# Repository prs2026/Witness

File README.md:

# Witness
Witness flight computer

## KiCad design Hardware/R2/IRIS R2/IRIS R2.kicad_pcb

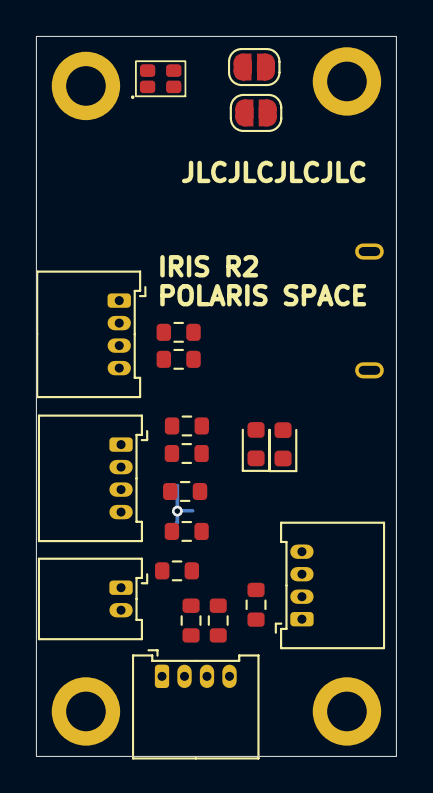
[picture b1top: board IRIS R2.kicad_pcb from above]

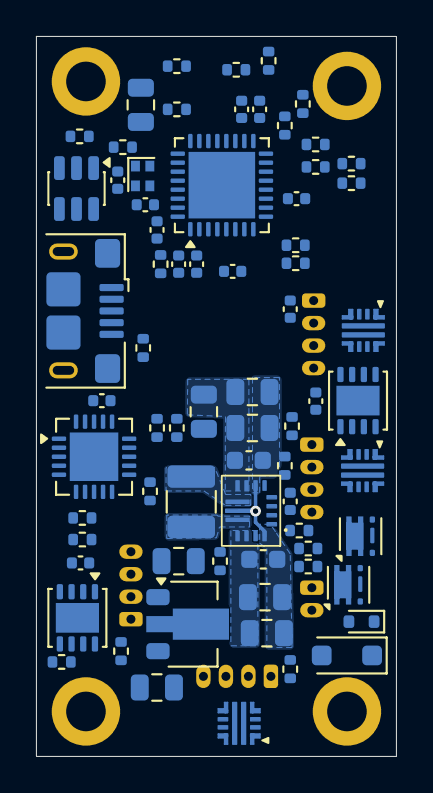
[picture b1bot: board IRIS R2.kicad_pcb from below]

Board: 4 copper layers, 20.0 x 40.0 mm, 95 parts (71 on the bottom side), 65 nets.

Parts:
C3, C4, C5, C7, C8, C9, C13, C21, C26, C27, C28, C29, C30: 100n; C_0402_1005Metric
C6: 1u; C_0402_1005Metric
C10, C11, C12, C18, C19: 10u; C_0805_2012Metric
C20, C22: 10u; C_0603_1608Metric
C23, C24, C25: 22u; C_0805_2012Metric
D1: LED_RGBA; 0603x2 RGB
D2, D3: LED; LED_0603_1608Metric
D4: PMEG2020EH,115; D_SOD-123F
D5: BZX584C10; D_SOD-523
H4, H5, H6, H7: MountingHole_Pad; MountingHole_2.2mm_M2_DIN965_Pad
J1, J4: Conn_01x02; SolderJumper-2_P1.3mm_Open_RoundedPad1.0x1.5mm
J2: Conn_01x02; Molex_Micro_Lock_2200980271_01x02_Horizontal
J3: USB_B_Micro; USB_Micro-B_Amphenol_10118193-0002LF_Horizontal
J5, J6, J7, J8: Conn_01x04; Molex_MicroLock-2200980471-01x04-Horizontal
L3: 1u; L_1210_3225Metric
Q1, Q2: SQA403EJ; Vishay_PowerPAK_SC70-6L_Single
R1, R2, R3, R4, R5, R11, R13: 0; R_0603_1608Metric
R6, R10, R12, R55: 10k; R_0402_1005Metric
R7: 680k; R_0402_1005Metric
R8: 130k; R_0402_1005Metric
R9: 100k; R_0402_1005Metric
R17, R18, R19, R20, R22, R38: 1k; R_0402_1005Metric
R21: 15k; R_0402_1005Metric
R23, R24, R25, R26: 4.7k; R_0402_1005Metric
R30, R31, R33, R34, R35, R36, R37, R47, R50, R51: 0; R_0402_1005Metric
R32: 5k; R_0402_1005Metric
R39: 120; R_0402_1005Metric
R45, R46, R56: 20m; R_0603_1608Metric
U1, U5, U10: TPS259472ARPWR; QFN-10-2x2-hotrod
U2: ME6118A33PG; SOT-89-3
U3: TLA2528IR; VSON-8-1EP_3x3mm_P0.65mm_EP1.65x2.4mm
U4: MCP23008-xML; QFN-20-1EP_4x4mm_P0.5mm_EP2.7x2.7mm
U6: TPS63070; RNM0015A
U7: ESP32-C3FH4; QFN-32-1EP_5x5mm_P0.5mm_EP3.7x3.7mm
U8: TCAN3414DRBR; VSON-8-1EP_3x3mm_P0.65mm_EP1.65x2.4mm
U9: USBLC6-2SC6; SOT-23-6
Y1: F322540MUBCE2O; Oscillator_SMD_Abracon_ASCO-4Pin_1.6x1.2mm

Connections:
+3V3: C3.1, C4.1, C5.1, C6.1, C7.2, C8.1, C9.1, C11.1, C12.1, C26.1, C27.1, C28.1, C29.1, C30.1, D1.4 (A), D2.2 (A), R13.2, R22.2, R23.2, R24.2, R25.2, R26.2, U2.2 (VOUT), U3.7 (AVDD), U4.18 (VDD), U7.2 (VDD3P3), U7.3 (VDD3P3), U7.11 (VDD3P3_RTC), U7.17 (VDD3P3_CPU), U7.18 (VDD_SPI), U7.31 (VDDA), U7.32 (VDDA), U8.3 (VCC), Y1.1 (Tri-State), Y1.4 (VDD)
+5V: C22.1, C23.1, C24.1, C25.1, D3.2 (A), R2.1, R4.1, R7.1, R9.1, R11.1, R46.2, U6.7 (VOUT), U6.8 (VOUT)
+BATT: C18.1, C19.1, C20.1, D4.1 (K), Q2.4 (S), R1.1, R3.1, R5.1, R6.1, R12.1, R21.2, R45.1, U6.12 (VIN), U6.13 (VIN)
/IO/BATT_RAW: J2.1, Q1.1 (D)
/IO/CANRX: R34.2, U8.1 (TXD)
/IO/CANTX: R33.2, U8.4 (RXD)
/IO/CAN_H: J6.3, R39.2, U8.7 (CANH)
/IO/CAN_L: J6.2, R39.1, U8.6 (CANL)
/IO/OUT1PWR: J5.1, U5.5 (OUT)
/IO/OUT2PWR: J7.1, U3.3 (AIN4), U10.5 (OUT)
/IO/OUT3PWR: J8.1, U1.5 (OUT), U3.1 (AIN2)
/IO/RXD0_MCU: J7.3, R50.2
/IO/RXD1_MCU: J5.3, R36.2
/IO/TXD0_MCU: J7.2, R37.2
/IO/TXD1_MCU: J5.2, R35.2
/IO/USB_D+: J3.3 (D+), R31.1, U9.1 (I/O1), U9.6 (I/O1)
/IO/USB_D-: J3.2 (D-), R30.1, U9.3 (I/O2), U9.4 (I/O2)
/Load Switches/CS2: U1.9 (ILM), U3.2 (AIN3)
/Load Switches/CS3: U3.4 (AIN5), U10.9 (ILM)
/Load Switches/EN1: U4.9 (GP0), U5.1 (EN/UVLO)
/Load Switches/EN2: U1.1 (EN/UVLO), U4.10 (GP1)
/Load Switches/EN3: U4.11 (GP2), U10.1 (EN/UVLO)
/Load Switches/SCL: R26.1, U4.19 (SCL), U7.10 (MTDI)
/Load Switches/SDA: R25.1, U4.20 (SDA), U7.9 (MTMS)
/Load Switches/VIN1: R1.2, R2.2, U5.6 (VIN)
/Load Switches/VIN2: R3.2, R4.2, U1.6 (VIN)
/Load Switches/VIN3: R5.2, R11.2, U10.6 (VIN)
/MCU/5V_EN: R12.2, U4.12 (GP3), U6.14 (EN)
/MCU/BUTTON: R24.1, U7.6 (GPIO2)
/MCU/CANRX: R34.1, U7.8 (GPIO3)
/MCU/CANTX: R33.1, U7.5 (XTAL_32K_N)
/MCU/LED_B: R19.1, U4.16 (GP7)
/MCU/LED_G: R17.1, U7.16 (GPIO10)
/MCU/LED_R: R18.1, U7.14 (GPIO8)
/MCU/LS_EN: J4.1, R23.1, R55.2, U4.4 (~RESET), U7.15 (GPIO9)
/MCU/RST: J1.1, R22.1, U7.7 (CHIP_EN)
/MCU/RXD0_MCU: R50.1, U7.27 (U0RXD)
/MCU/RXD1_MCU: R36.1, U7.13 (MTDO)
/MCU/TXD0_MCU: R37.1, U7.28 (U0TXD)
/MCU/TXD1_MCU: R35.1, U7.12 (MTCK)
/MCU/VSENSE: R21.1, R32.2, U7.4 (XTAL_32K_P)
/MCU/XIN: U7.30 (XTAL_P), Y1.3 (OUT)
GND: C3.2, C4.2, C5.2, C6.2, C7.1, C8.2, C9.2, C10.2, C11.2, C12.2, C13.1, C18.2, C19.2, C20.2, C21.2, C22.2, C23.2, C24.2, C25.2, C26.2, C27.2, C28.2, C29.2, C30.2, H4.1 (1_1), H5.1 (1_1), H6.1 (1_1), H7.1 (1_1), J1.2, J2.2, J3.5 (GND), J4.2, J5.4, J6.4, J7.4, J8.4, R8.2, R10.2, R20.1, R32.1, R38.1, R47.1, R51.1, R55.1, U1.2 (OVLO/OVCSEL), U1.8 (GND), U2.1 (GND), U3.9 (GND), U4.1 (A2), U4.2 (A1), U4.3 (A0), U4.17 (VSS), U5.2 (OVLO/OVCSEL), U5.8 (GND), U6.4 (GND), U6.6 (FB2), U6.10 (PGND), U6.15 (VSEL), U7.33 (GND), U8.2 (GND), U9.2 (GND), U10.2 (OVLO/OVCSEL), U10.8 (GND), Y1.2 (GND)
unnamed: D1.3 (BK), R19.2
unnamed: D1.2 (GK), R17.2
unnamed: D1.1 (RK), R18.2
unnamed: D2.1 (K), R20.2
unnamed: D3.1 (K), R38.2
unnamed: D5.2 (A), Q1.3 (G), R10.1
unnamed: D5.1 (K), Q1.4 (S), Q2.1 (D)
unnamed: J3.SH (Shield), R47.2
unnamed: J3.1 (VBUS), R56.1
unnamed: J6.1, R13.1
unnamed: C10.1, R45.2, R46.1, U2.3 (VIN)
unnamed: C13.2, U3.8 (DECAP)
unnamed: R7.2, R8.1, U6.5 (FB)
unnamed: L3.1, U6.11 (L1)
unnamed: L3.2, U6.9 (L2)
unnamed: R9.2, U6.2 (PG)
unnamed: R6.2, U6.1 (PS/SYNC)
unnamed: C21.1, U6.3 (VAUX)
unnamed: R30.2, U7.25 (GPIO18)
unnamed: R31.2, U7.26 (GPIO19)
unnamed: R51.2, U8.8 (STB)
VBUS: D4.2 (A), Q2.3 (G), R56.2, U9.5 (VBUS)

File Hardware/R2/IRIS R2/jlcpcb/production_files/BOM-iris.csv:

Comment,Designator,Footprint,LCSC,Quantity
0,R51,R_0402_1005Metric,C11702,1
0,"R30,R31,R33,R34,R35,R36,R37,R47,R50",R_0402_1005Metric,C17168,9
0,"R13,R2,R4,R5",R_0603_1608Metric,C21189,4
100k,R9,R_0402_1005Metric,C25741,1
100n,"C21,C26,C27,C28,C29,C3,C30,C4,C5,C7,C8,C9",C_0402_1005Metric,C307331,12
10k,"R10,R52,R53,R54,R55,R6",R_0402_1005Metric,C25744,6
10u,"C10,C11,C12,C18,C19",C_0805_2012Metric,C440198,5
10u,"C20,C22",C_0603_1608Metric,C96446,2
120,R39,R_0402_1005Metric,C25079,1
130k,R8,R_0402_1005Metric,C881362,1
1k,"R17,R18,R19,R20,R22,R38,R40,R41,R46,R48",R_0402_1005Metric,C11702,10
1u,L3,L_1210_3225Metric,C237284,1
1u,C6,C_0402_1005Metric,C52923,1
20m,"R43,R44,R49",R_0603_1608Metric,C911681,3
22u,"C23,C24,C25",C_0805_2012Metric,C45783,3
4.7k,"R23,R24,R25,R26",R_0402_1005Metric,C25900,4
680k,R7,R_0402_1005Metric,C409718,1
AO3400A,"Q11,Q4,Q5",SOT-23,C20917,3
BZX584C10,D5,D_SOD-523,C22395577,1
ESP32-C3FH4,U7,QFN-32-1EP_5x5mm_P0.5mm_EP3.7x3.7mm,C2858491,1
F322540MUBCE2O,Y1,Oscillator_SMD_Abracon_ASCO-4Pin_1.6x1.2mm,C5917310,1
MCP23008-xML,U4,QFN-20-1EP_4x4mm_P0.5mm_EP2.7x2.7mm,C623183,1
ME6118A33PG,U2,SOT-89-3,C236721,1
PAC1934x-xJQ,U1,UQFN-16-1EP_4x4mm_P0.65mm_EP2.6x2.6mm,C623960,1
"PMEG2020EH,115",D4,D_SOD-123F,C456104,1
SQA403EJ,"Q1,Q12,Q2,Q3,Q6",Vishay_PowerPAK_SC70-6L_Single,C7083947,5
TCAN1044A-Q1,U5,VSON-8-1EP_3x3mm_P0.65mm_EP1.65x2.4mm,C3234119,1
TPS63070,U6,RNM0015A,C109322,1
USBLC6-2SC6,U9,SOT-23-6,C7519,1
USB_B_Micro,J3,USB_Micro-B_Amphenol_10118193-0002LF_Horizontal,C132562,1
Conn_01x02,J4,SolderJumper-2_P1.3mm_Open_RoundedPad1.0x1.5mm,,1
Conn_01x04,J5,Molex_MicroLock-2200980471-01x04-Horizontal,,1
Conn_01x02,J1,SolderJumper-2_P1.3mm_Open_RoundedPad1.0x1.5mm,,1
Conn_01x04,J6,Molex_MicroLock-2200980471-01x04-Horizontal,,1
MountingHole_Pad,H6,MountingHole_2.2mm_M2_DIN965_Pad,,1
MountingHole_Pad,H5,MountingHole_2.2mm_M2_DIN965_Pad,,1
LED_RGBA,D1,0603x2 RGB,,1
Conn_01x02,J2,Molex_Micro_Lock_2200980271_01x02_Horizontal,,1
MountingHole_Pad,H7,MountingHole_2.2mm_M2_DIN965_Pad,,1
LED,D2,LED_0603_1608Metric,,1
MountingHole_Pad,H4,MountingHole_2.2mm_M2_DIN965_Pad,,1
15k,R21,R_0402_1005Metric,,1
LTV-817S,U3,SMDIP-4_W9.53mm,,1
5k,R32,R_0402_1005Metric,,1
Conn_01x04,J8,Molex_MicroLock-2200980471-01x04-Horizontal,,1
Conn_01x04,J7,Molex_MicroLock-2200980471-01x04-Horizontal,,1
LED,D3,LED_0603_1608Metric,,1

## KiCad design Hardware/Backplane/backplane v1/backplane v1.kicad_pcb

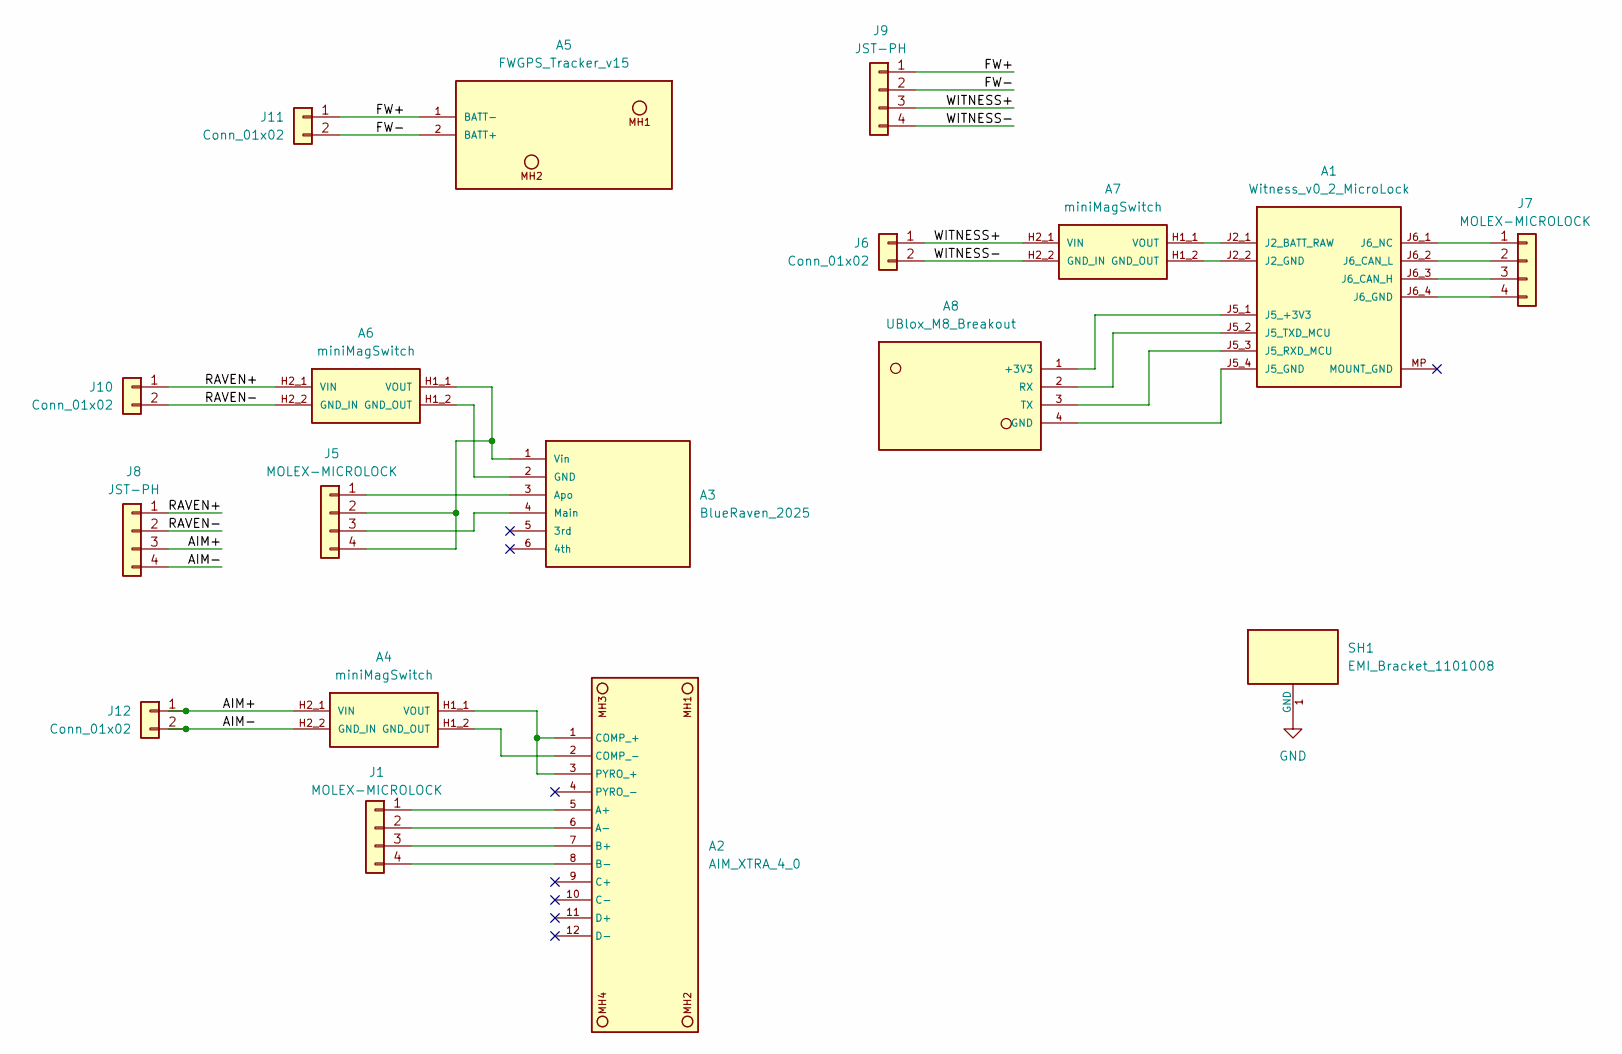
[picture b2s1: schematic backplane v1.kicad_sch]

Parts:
A1: Witness_v0_2_MicroLock
A2: AIM_XTRA_4_0; AIM_XTRA_4_0_Location_Template
A3: BlueRaven_2025; BlueRaven_2025_Location_Template
A4, A6, A7: miniMagSwitch; miniMagSwitch_SideOn_DualHeader
A5: FWGPS_Tracker_v15; FWGPS_Tracker_v15_Location_Template
A8: UBlox_M8_Breakout
J1, J5, J7: MOLEX-MICROLOCK; CONN_2200980000-SD_04P_MOL
J6, J10, J11, J12: Conn_01x02; CONN_B02B-PASK-1_JST
J8, J9: JST-PH; JST_PH_B4B-PH-K_1x04_P2.00mm_Vertical
SH1: EMI_Bracket_1101008

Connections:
/AIM+: A4.H2_1 (VIN), J8.3, J12.1
/AIM-: A4.H2_2 (GND_IN), J8.4, J12.2
/FW+: A5.1 (BATT-), J9.1, J11.1
/FW-: A5.2 (BATT+), J9.2, J11.2
/RAVEN+: A6.H2_1 (VIN), J8.1, J10.1
/RAVEN-: A6.H2_2 (GND_IN), J8.2, J10.2
/WITNESS+: A7.H2_1 (VIN), J6.1, J9.3
/WITNESS-: A7.H2_2 (GND_IN), J6.2, J9.4
GND: SH1.1 (GND_1)
unnamed: A1.J2_1 (J2_BATT_RAW), A7.H1_1 (VOUT)
unnamed: A1.J2_2 (J2_GND), A7.H1_2 (GND_OUT)
unnamed: A1.J5_1 (J5_+3V3), A8.1 (+3V3)
unnamed: A1.J5_4 (J5_GND), A8.4 (GND)
unnamed: A1.J5_3 (J5_RXD_MCU), A8.3 (TX)
unnamed: A1.J5_2 (J5_TXD_MCU), A8.2 (RX)
unnamed: A1.J6_3 (J6_CAN_H), J7.3
unnamed: A1.J6_2 (J6_CAN_L), J7.2
unnamed: A1.J6_4 (J6_GND), J7.4
unnamed: A1.J6_1 (J6_NC), J7.1
unnamed: A2.5 (A+), J1.1
unnamed: A2.6 (A-), J1.2
unnamed: A2.7 (B+), J1.3
unnamed: A2.8 (B-), J1.4
unnamed: A2.1 (COMP_+), A2.3 (PYRO_+), A4.H1_1 (VOUT)
unnamed: A2.2 (COMP_-), A4.H1_2 (GND_OUT)
unnamed: A3.3 (Apo), J5.1
unnamed: A3.2 (GND), A6.H1_2 (GND_OUT)
unnamed: A3.4 (Main), J5.3
unnamed: A3.1 (Vin), A6.H1_1 (VOUT), J5.2, J5.4

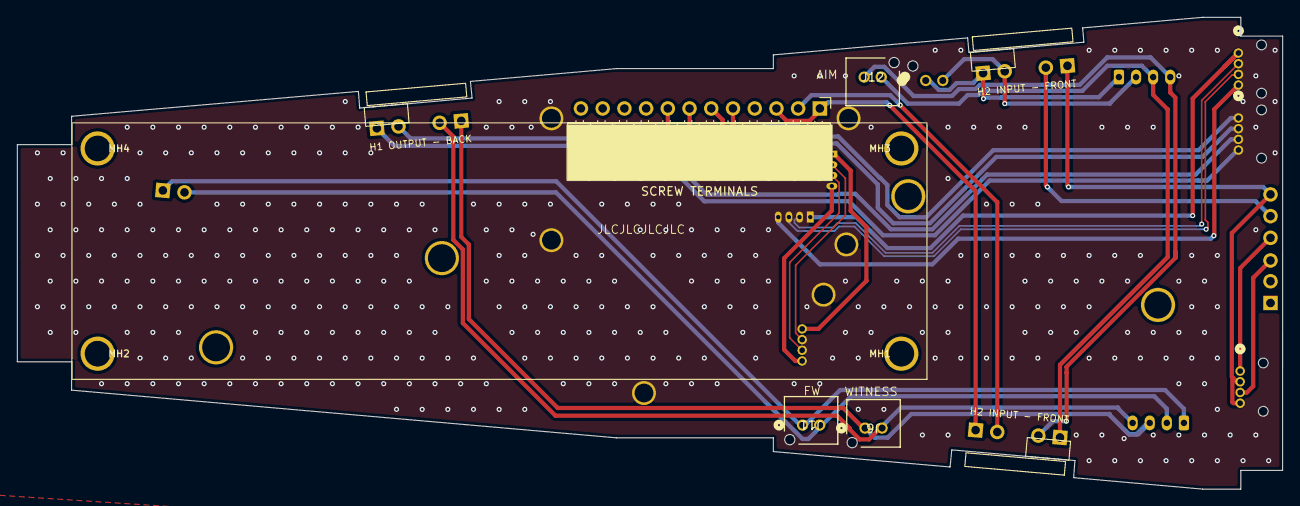
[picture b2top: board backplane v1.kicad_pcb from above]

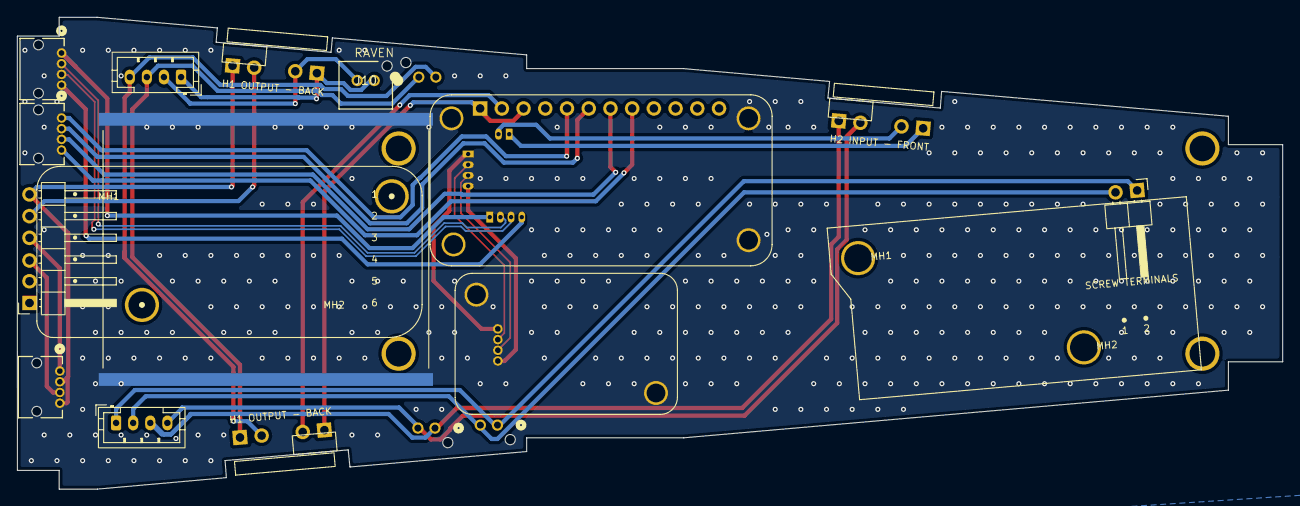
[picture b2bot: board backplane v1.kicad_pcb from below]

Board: 2 copper layers, 148.0 x 55.2 mm, 18 parts (12 on the bottom side), 28 nets.

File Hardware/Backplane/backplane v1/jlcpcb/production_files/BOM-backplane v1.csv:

Comment,Designator,Footprint,LCSC,Quantity
EMI_Bracket_1101008,SH1,EMI_Bracket_1101008,,1
Conn_01x02,J6,CONN_B02B-PASK-1_JST,,1
miniMagSwitch,A4,miniMagSwitch_SideOn_DualHeader,,1
miniMagSwitch,A6,miniMagSwitch_SideOn_DualHeader,,1
MOLEX-MICROLOCK,J7,CONN_2200980000-SD_04P_MOL,,1
UBlox_M8_Breakout,A8,UBlox_M8_Breakout,,1
MOLEX-MICROLOCK,J1,CONN_2200980000-SD_04P_MOL,,1
JST-PH,J8,JST_PH_B4B-PH-K_1x04_P2.00mm_Vertical,,1
MOLEX-MICROLOCK,J5,CONN_2200980000-SD_04P_MOL,,1
Witness_v0_2_MicroLock,A1,Witness_v0_2_MicroLock,,1
miniMagSwitch,A7,miniMagSwitch_SideOn_DualHeader,,1
JST-PH,J9,JST_PH_B4B-PH-K_1x04_P2.00mm_Vertical,,1
Conn_01x02,J12,CONN_B02B-PASK-1_JST,,1
Conn_01x02,J11,CONN_B02B-PASK-1_JST,,1
Conn_01x02,J10,CONN_B02B-PASK-1_JST,,1

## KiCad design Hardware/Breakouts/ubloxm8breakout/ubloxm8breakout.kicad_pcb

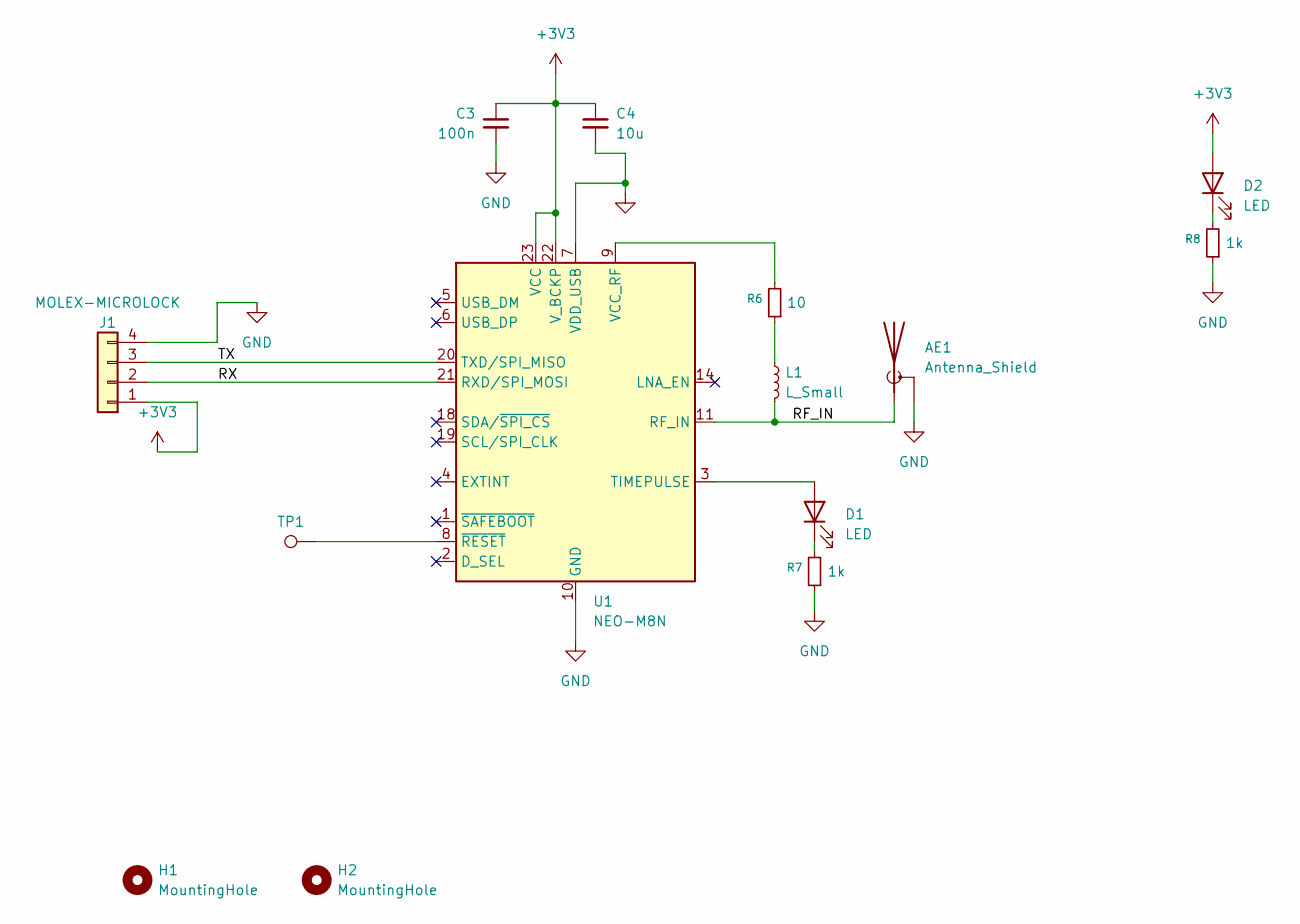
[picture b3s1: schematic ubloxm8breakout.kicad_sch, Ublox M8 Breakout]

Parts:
AE1: Antenna_Shield; U.FL_Molex_MCRF_73412-0110_Vertical
C3: 100n; C_0603_1608Metric
C4: 10u; C_0603_1608Metric
D1, D2: LED; LED_0603_1608Metric
H1, H2: MountingHole; MountingHole_2.2mm_M2
J1: MOLEX-MICROLOCK; CONN_2200980000-SD_04P_MOL
L1: L_Small; L_0603_1608Metric
R6: 10; R_0603_1608Metric
R7, R8: 1k; R_0603_1608Metric
TP1: TestPoint; TestPoint_Pad_1.5x1.5mm
U1: NEO-M8N; ublox_NEO

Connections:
+3V3: C3.1, C4.1, D2.2 (A), J1.1, U1.22 (V_BCKP), U1.23 (VCC)
/RF_IN: AE1.1 (A), L1.2, U1.11 (RF_IN)
/RX: J1.2, U1.21 (RXD/SPI_MOSI)
/TX: J1.3, U1.20 (TXD/SPI_MISO)
GND: AE1.2 (Shield), C3.2, C4.2, J1.4, R7.1, R8.1, U1.7 (VDD_USB), U1.10 (GND), U1.12 (GND), U1.13 (GND), U1.24 (GND)
unnamed: D1.2 (A), U1.3 (TIMEPULSE)
unnamed: D1.1 (K), R7.2
unnamed: D2.1 (K), R8.2
unnamed: L1.1, R6.1
unnamed: R6.2, U1.9 (VCC_RF)
unnamed: TP1.1 (1_1), U1.8 (~RESET)

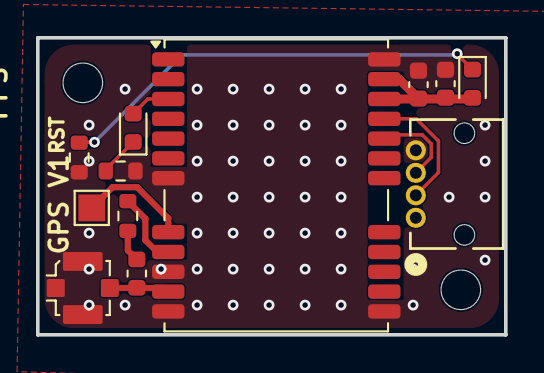
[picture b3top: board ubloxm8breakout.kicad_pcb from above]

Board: 4 copper layers, 26.0 x 16.5 mm, 14 parts (0 on the bottom side), 11 nets.

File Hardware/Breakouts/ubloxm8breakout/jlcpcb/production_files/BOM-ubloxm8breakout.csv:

Comment,Designator,Footprint,LCSC,Quantity
LED,D1,LED_0603_1608Metric,,1
MOLEX-MICROLOCK,J1,CONN_2200980000-SD_04P_MOL,,1
L_Small,L1,L_0603_1608Metric,,1
NEO-M8N,U1,ublox_NEO,,1
10,R6,R_0603_1608Metric,,1
100n,C3,C_0603_1608Metric,,1
LED,D2,LED_0603_1608Metric,,1
1k,R8,R_0603_1608Metric,,1
Antenna_Shield,AE1,U.FL_Molex_MCRF_73412-0110_Vertical,,1
TestPoint,TP1,TestPoint_Pad_1.5x1.5mm,,1
1k,R7,R_0603_1608Metric,,1
10u,C4,C_0603_1608Metric,,1

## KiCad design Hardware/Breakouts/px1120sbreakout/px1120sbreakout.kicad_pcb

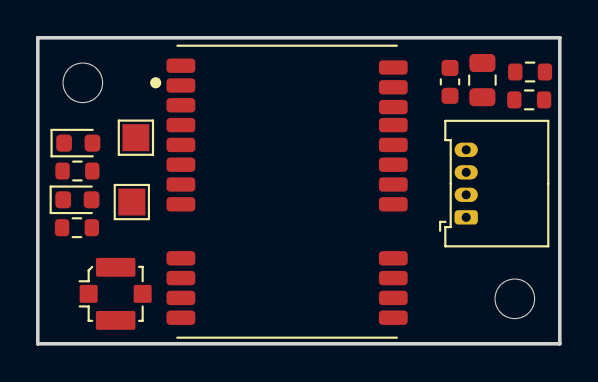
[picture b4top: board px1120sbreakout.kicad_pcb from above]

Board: 2 copper layers, 29.0 x 17.0 mm, 15 parts (0 on the bottom side), 12 nets, no tracks yet.

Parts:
AE1: Antenna_Shield; U.FL_Molex_MCRF_73412-0110_Vertical
C1: 10u; C_0805_2012Metric
C3: 100n; C_0603_1608Metric
D1, D2: LED; LED_0603_1608Metric
H1, H2: MountingHole; MountingHole_2.2mm_M2
J1: MOLEX-MICROLOCK; Molex_MicroLock-2200980471-01x04-Horizontal
R3, R4: 0; R_0603_1608Metric
R7, R8: 1k; R_0603_1608Metric
TP1, TP2: TestPoint; TestPoint_Pad_1.5x1.5mm
U1: PX1120S

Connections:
+3V3: C1.1, C3.1, D2.2 (A), J1.1, U1.22 (V_BCKP), U1.23 (VCC)
GND: AE1.2 (Shield), C1.2, C3.2, J1.4, R7.1, R8.1, U1.10 (GND), U1.12 (GND), U1.13 (GND), U1.24 (GND)
unnamed: AE1.1 (A), U1.11 (RF_IN)
unnamed: D1.2 (A), U1.3 (1PPS)
unnamed: D1.1 (K), R7.2
unnamed: D2.1 (K), R8.2
unnamed: J1.2, R3.2
unnamed: J1.3, R4.2
unnamed: TP1.1 (1_1), U1.1 (BOOT_SEL)
unnamed: TP2.1 (1_1), U1.8 (RSTN)
unnamed: R3.1, U1.21 (RXD)
unnamed: R4.1, U1.20 (TXD)

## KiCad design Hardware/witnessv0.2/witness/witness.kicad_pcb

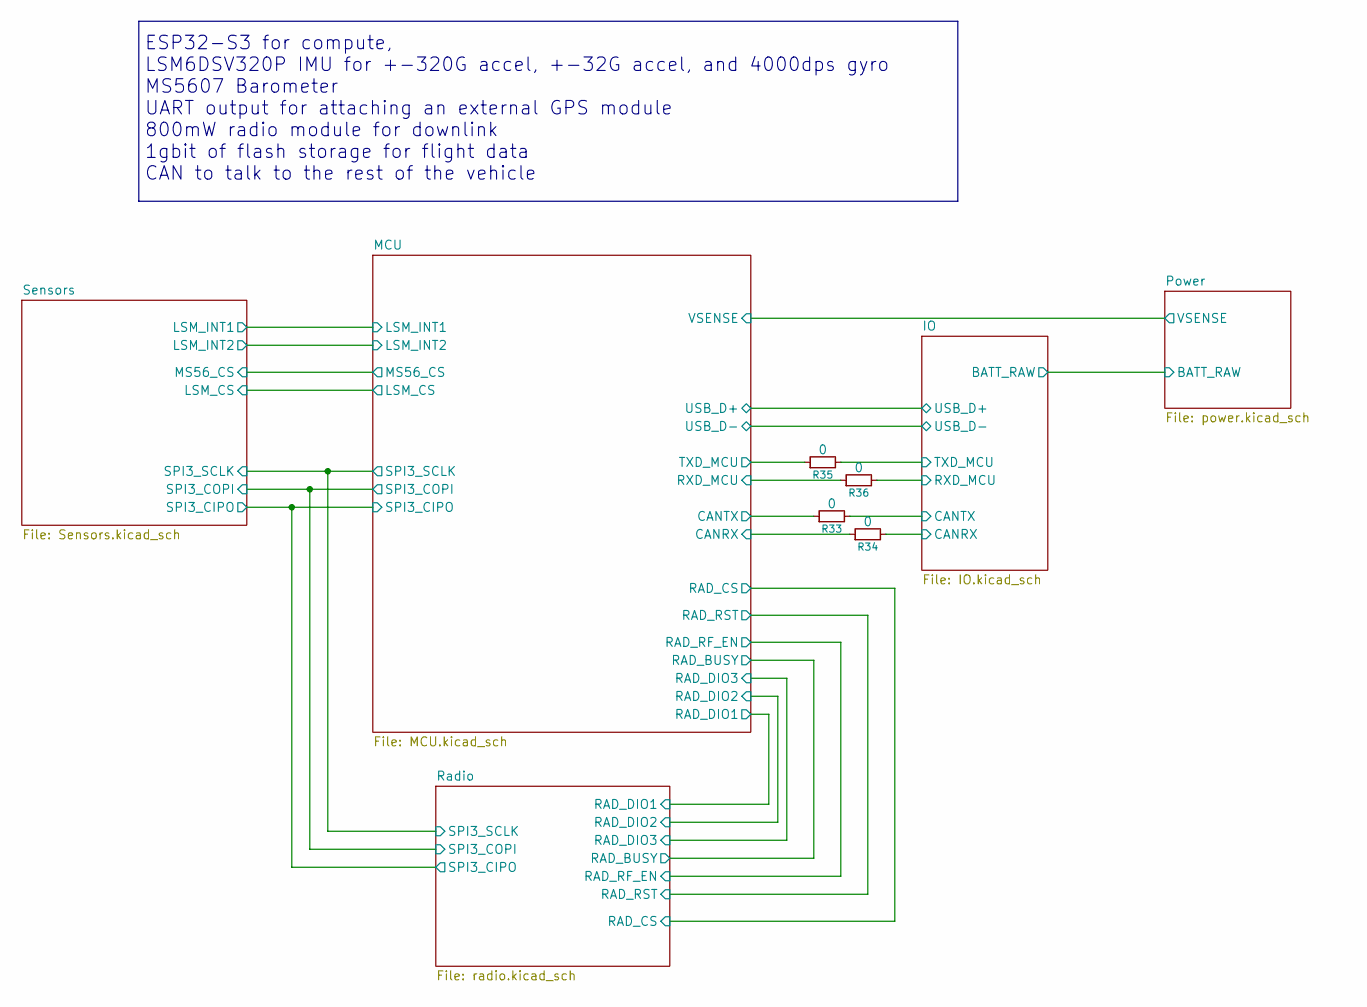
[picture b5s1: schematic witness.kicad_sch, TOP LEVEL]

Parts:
R33, R34, R35, R36: 0; R_0402_1005Metric; LCSC_Part C17168

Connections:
/IO/CANRX: R34.2; also elsewhere on the board
/IO/CANTX: R33.2; also elsewhere on the board
/IO/RXD_MCU: R36.2; also elsewhere on the board
/IO/TXD_MCU: R35.2; also elsewhere on the board
/MCU/CANRX: R34.1; also elsewhere on the board
/MCU/CANTX: R33.1; also elsewhere on the board
/MCU/RXD_MCU: R36.1; also elsewhere on the board
/MCU/TXD_MCU: R35.1; also elsewhere on the board

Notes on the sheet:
ESP32-S3 for compute, LSM6DSV320P IMU for +-320G accel, +-32G accel, and 4000dps gyro MS5607 Barometer UART output for attaching an external GPS module 800mW radio module for downlink 1gbit of flash storage for flight data CAN to talk to the rest of the vehicle

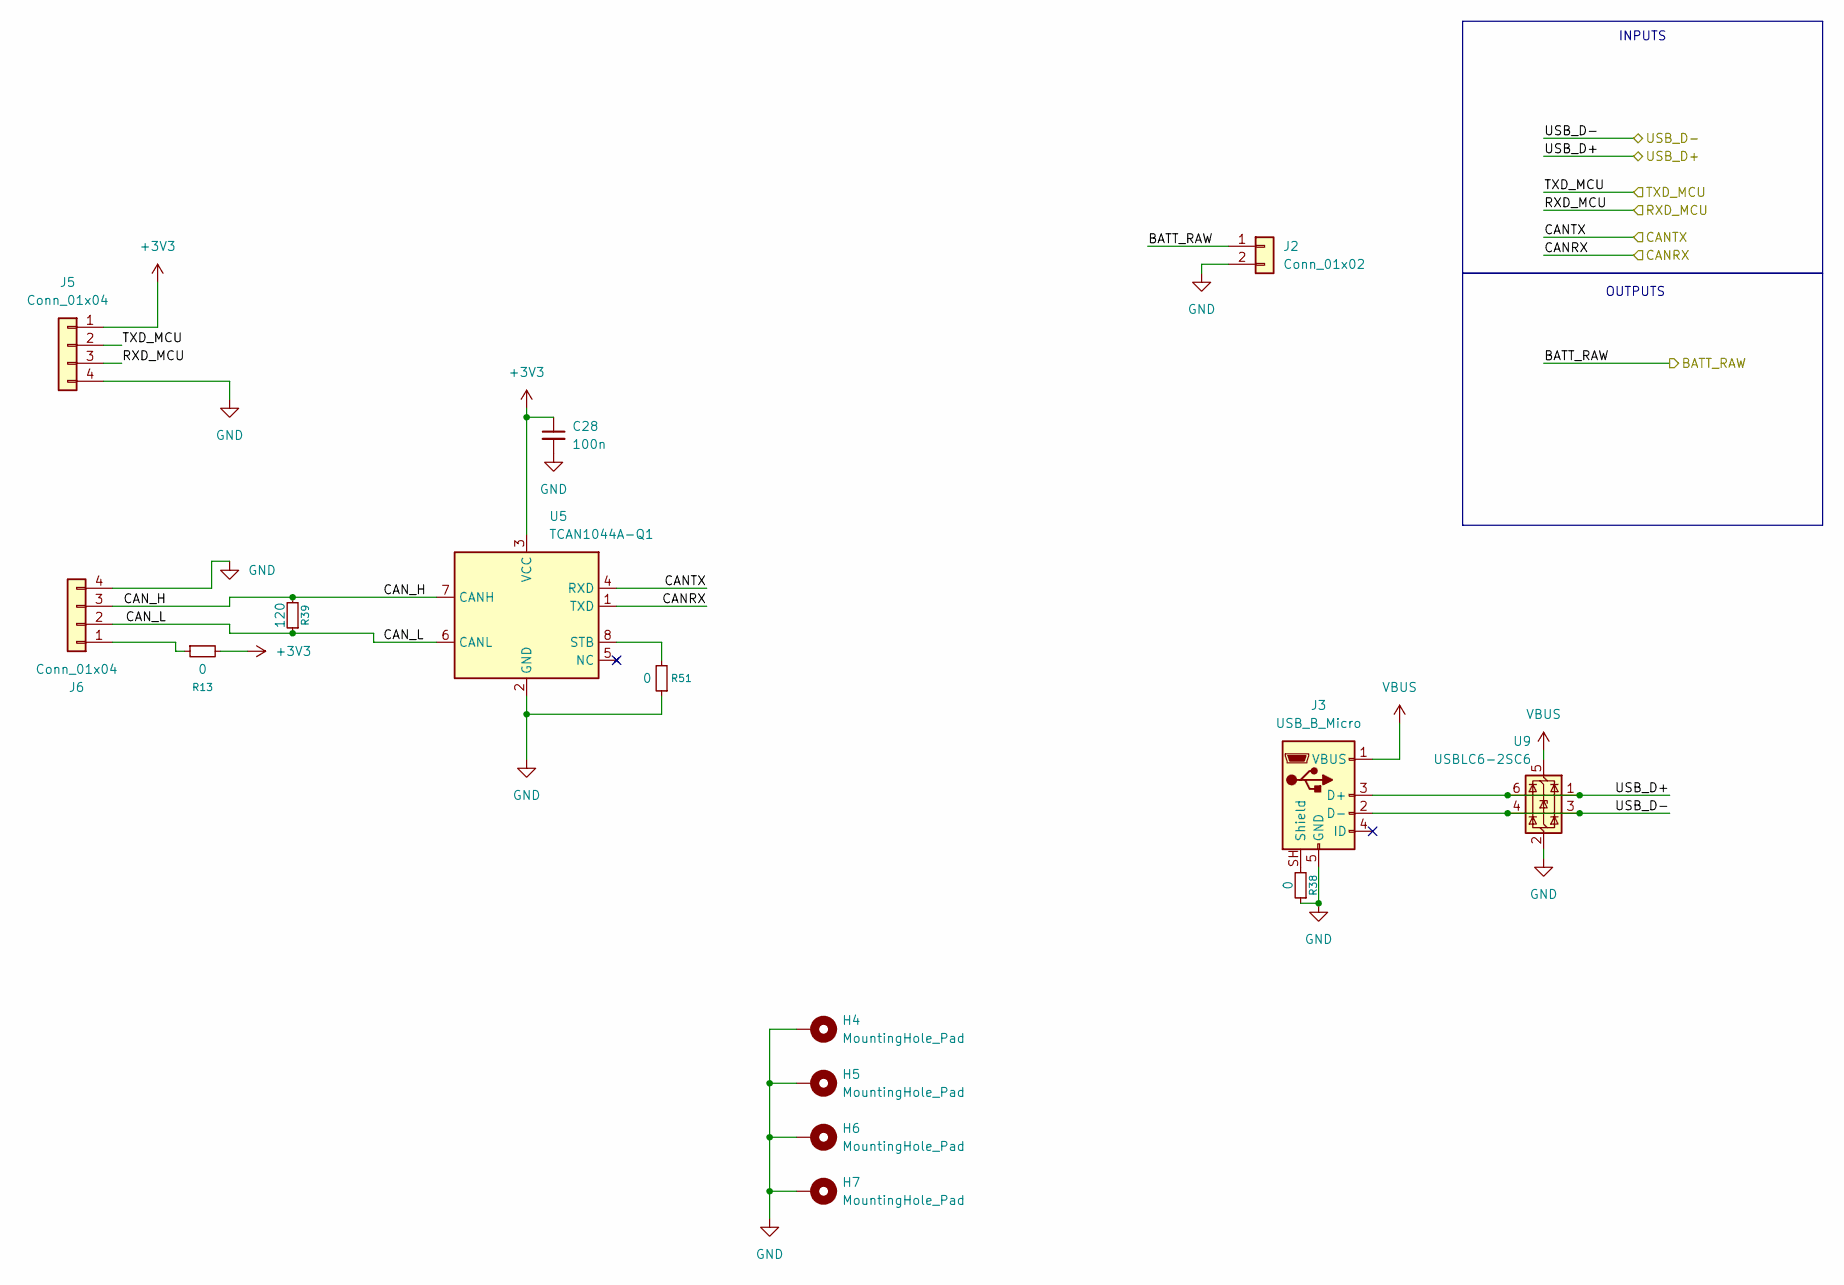
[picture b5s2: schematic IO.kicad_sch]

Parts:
C28: 100n; C_0402_1005Metric; LCSC_Part C307331
H4, H5, H6, H7: MountingHole_Pad; MountingHole_2.2mm_M2_DIN965_Pad
J2: Conn_01x02; Molex_Micro_Lock_2200980271_01x02_Horizontal
J3: USB_B_Micro; USB_Micro-B_Amphenol_10118193-0002LF_Horizontal; LCSC_Part C132562
J5, J6: Conn_01x04; Molex_MicroLock-2200980471-01x04-Horizontal
R13: 0; R_0603_1608Metric
R38, R51: 0; R_0402_1005Metric; LCSC_Part C17168
R39: 120; R_0402_1005Metric; LCSC_Part C25079
U5: TCAN1044A-Q1; VSON-8-1EP_3x3mm_P0.65mm_EP1.65x2.4mm; LCSC_Part C3234119
U9: USBLC6-2SC6; SOT-23-6; LCSC_Part C7519

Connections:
+3V3: C28.1, J5.1, R13.2, U5.3 (VCC); also elsewhere on the board
/IO/BATT_RAW: J2.1; also elsewhere on the board
/IO/CANRX: U5.1 (TXD); also elsewhere on the board
/IO/CANTX: U5.4 (RXD); also elsewhere on the board
/IO/CAN_H: J6.3, R39.2, U5.7 (CANH)
/IO/CAN_L: J6.2, R39.1, U5.6 (CANL)
/IO/RXD_MCU: J5.3; also elsewhere on the board
/IO/TXD_MCU: J5.2; also elsewhere on the board
/IO/USB_D+: J3.3 (D+), U9.1 (I/O1), U9.6 (I/O1); also elsewhere on the board
/IO/USB_D-: J3.2 (D-), U9.3 (I/O2), U9.4 (I/O2); also elsewhere on the board
GND: C28.2, H4.1 (1_1), H5.1 (1_1), H6.1 (1_1), H7.1 (1_1), J2.2, J3.5 (GND), J5.4, J6.4, R38.1, R51.1, U5.2 (GND), U9.2 (GND); also elsewhere on the board
unnamed: J3.SH (Shield), R38.2
unnamed: J6.1, R13.1
unnamed: R51.2, U5.8 (STB)
VBUS: J3.1 (VBUS), U9.5 (VBUS); also elsewhere on the board

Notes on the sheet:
OUTPUTS
INPUTS

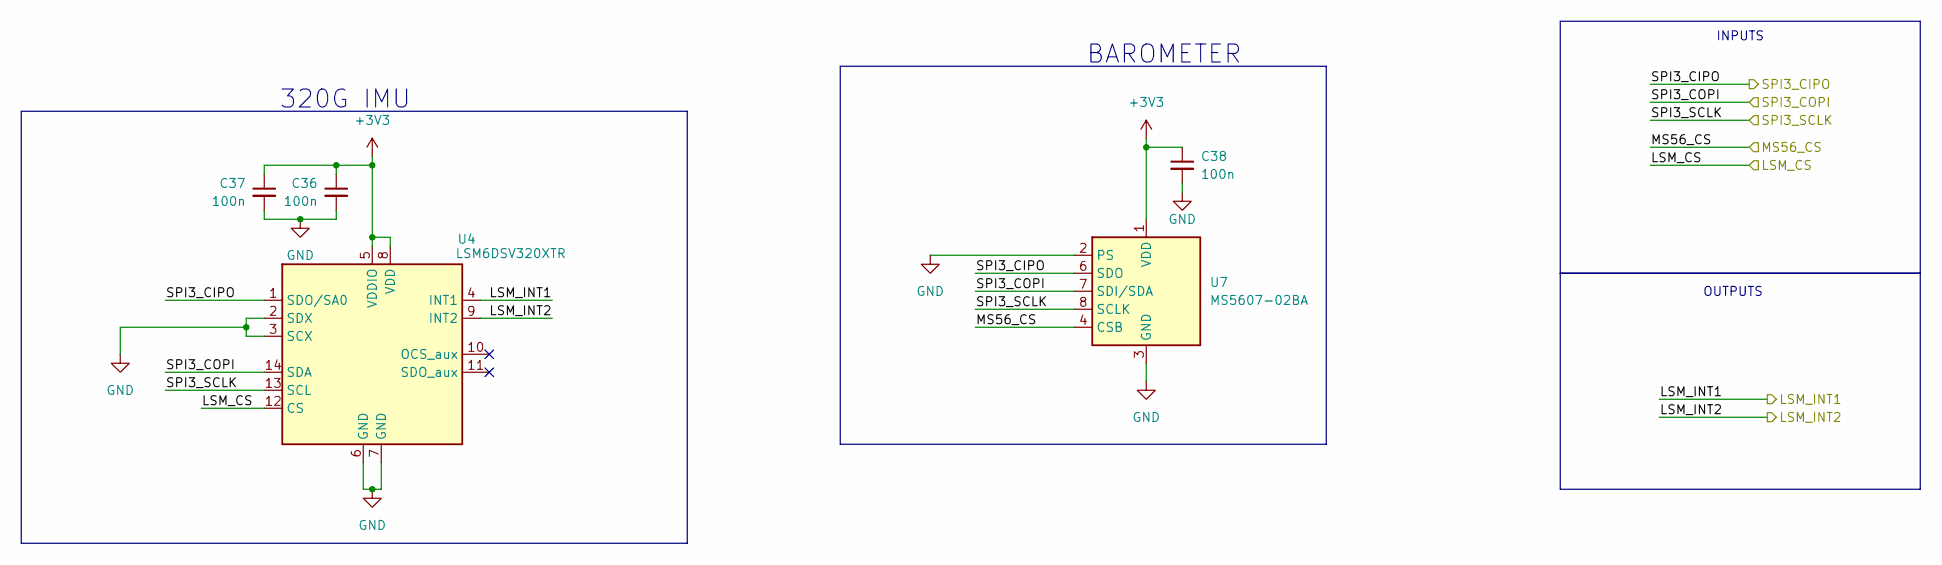
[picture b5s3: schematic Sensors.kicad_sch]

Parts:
C36, C37, C38: 100n; C_0402_1005Metric; LCSC_Part C307331
U4: LSM6DSV320XTR; Bosch_LGA-14_3x2.5mm_P0.5mm; LCSC_Part C26633007
U7: MS5607-02BA; LGA-8_3x5mm_P1.25mm; LCSC_Part C97627

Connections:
+3V3: C36.1, C37.1, C38.1, U4.5 (VDDIO), U4.8 (VDD), U7.1 (VDD); also elsewhere on the board
/MCU/LSM_CS: U4.12 (CS); also elsewhere on the board
/MCU/LSM_INT1: U4.4 (INT1); also elsewhere on the board
/MCU/LSM_INT2: U4.9 (INT2); also elsewhere on the board
/MCU/MS56_CS: U7.4 (CSB), U7.5 (CSB); also elsewhere on the board
/MCU/SPI3_CIPO: U4.1 (SDO/SA0), U7.6 (SDO); also elsewhere on the board
/MCU/SPI3_COPI: U4.14 (SDA), U7.7 (SDI/SDA); also elsewhere on the board
/MCU/SPI3_SCLK: U4.13 (SCL), U7.8 (SCLK); also elsewhere on the board
GND: C36.2, C37.2, C38.2, U4.2 (SDX), U4.3 (SCX), U4.6 (GND), U4.7 (GND), U7.2 (PS), U7.3 (GND); also elsewhere on the board

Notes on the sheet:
320G IMU
OUTPUTS
INPUTS
BAROMETER
